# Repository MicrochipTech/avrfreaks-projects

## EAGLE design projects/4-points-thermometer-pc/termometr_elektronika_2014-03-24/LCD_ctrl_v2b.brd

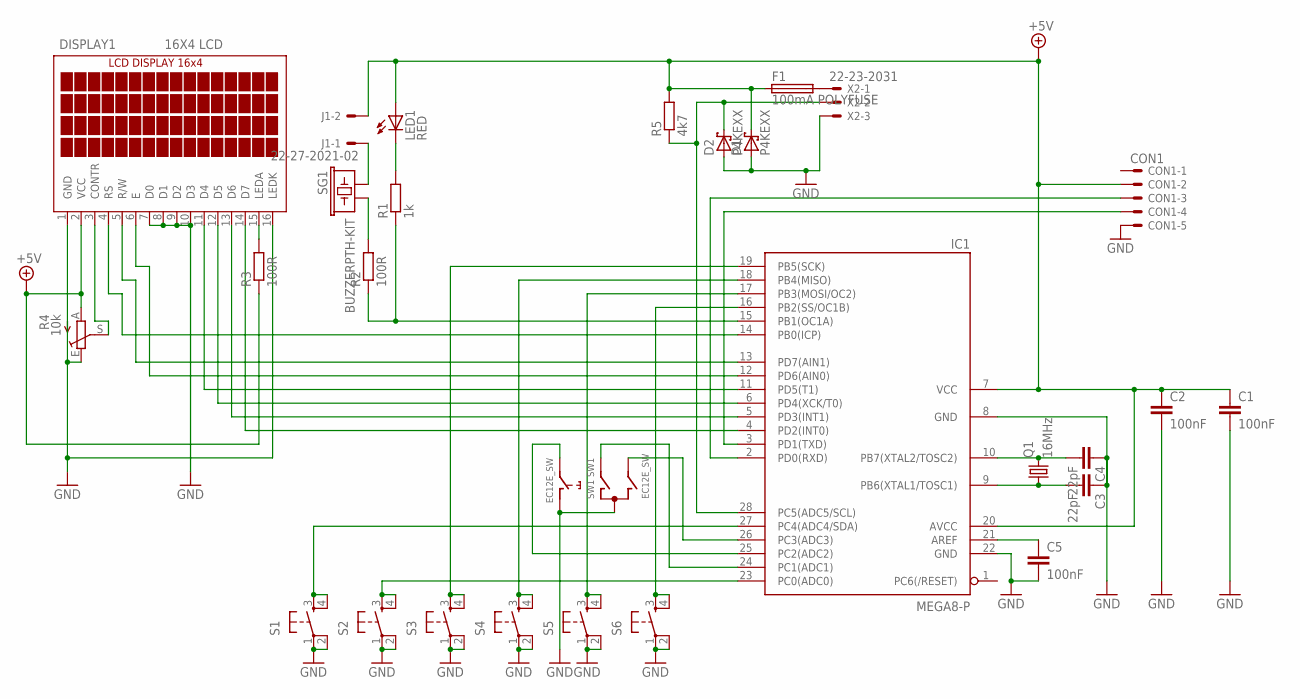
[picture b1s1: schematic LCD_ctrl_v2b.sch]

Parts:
C1, C2, C5: 100nF; C050-025X075
C3, C4: 22pF; C050-025X075
CON1: CON1; 22-23-2051
D1, D2: P4KEXX; DO41-10
DISPLAY1: 16X4 LCD; LCD-AC-1604A-BIG_PADS
F1: 100mA POLYFUSE; TE5
IC1: MEGA8-P; DIL28-3
J1: 22-27-2021-02; 6410-02
LED1: RED; LED3MM
Q1: 16MHz; HC49/S
R1: 1k; 0204/7
R2, R3: 100R; 0204/7
R4: 10k; CA6H
R5: 4k7; 0204/7
S1, S2, S3, S4, S5, S6: TAC_SWITCHPTH; TACTILE-PTHX
SG1: BUZZERPTH-KIT; BUZZER-12MM-KIT
SW1: EC12E_SW; ALPS_EC12E_SW
X2: 22-23-2031

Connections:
+5V: C1.1, C2.1, CON1.2, D1.C, DISPLAY1.2 (VCC), F1.1, IC1.7 (VCC), IC1.20 (AVCC), J1.2, LED1.A, R3.1, R4.A, R5.2
GND: C1.2, C2.2, C3.1, C4.1, C5.2, CON1.5, D1.A, D2.A, DISPLAY1.1 (GND), DISPLAY1.7 (D0), DISPLAY1.8 (D1), DISPLAY1.9 (D2), DISPLAY1.10 (D3), DISPLAY1.16 (LEDK), IC1.8 (GND), IC1.22 (GND), R4.E, S1.1, S1.2, S2.1, S2.2, S3.1, S3.2, S4.1, S4.2, S5.1, S5.2, S6.1, S6.2, SW1.C, SW1.D (1), X2.3
unnamed: C5.1, IC1.21 (AREF)
unnamed: F1.2, X2.1
unnamed: C4.2, IC1.10 (PB7(XTAL2/TOSC2)), Q1.2
unnamed: C3.2, IC1.9 (PB6(XTAL1/TOSC1)), Q1.1
unnamed: CON1.4, IC1.3 (PD1(TXD))
unnamed: CON1.3, IC1.2 (PD0(RXD))
unnamed: DISPLAY1.14 (D7), IC1.4 (PD2(INT0))
unnamed: DISPLAY1.13 (D6), IC1.5 (PD3(INT1))
unnamed: DISPLAY1.12 (D5), IC1.6 (PD4(XCK/T0))
unnamed: DISPLAY1.11 (D4), IC1.11 (PD5(T1))
unnamed: IC1.23 (PC0(ADC0)), S2.3, S2.4
unnamed: DISPLAY1.3 (CONTR), R4.S
unnamed: R2.2, SG1.- (2)
unnamed: DISPLAY1.6 (E), IC1.12 (PD6(AIN0))
unnamed: DISPLAY1.5 (R/W), IC1.13 (PD7(AIN1))
unnamed: LED1.K (C), R1.2
unnamed: DISPLAY1.4 (RS), IC1.14 (PB0(ICP))
unnamed: IC1.19 (PB5(SCK)), S3.3, S3.4
unnamed: IC1.18 (PB4(MISO)), S4.3, S4.4
unnamed: IC1.17 (PB3(MOSI/OC2)), S5.3, S5.4
unnamed: IC1.16 (PB2(SS/OC1B)), S6.3, S6.4
unnamed: IC1.24 (PC1(ADC1)), SW1.A
unnamed: J1.1, SG1.+ (1)
unnamed: DISPLAY1.15 (LEDA), R3.2
unnamed: IC1.25 (PC2(ADC2)), SW1.E (2)
unnamed: IC1.26 (PC3(ADC3)), SW1.B
unnamed: IC1.27 (PC4(ADC4/SDA)), S1.3, S1.4
unnamed: D2.C, IC1.28 (PC5(ADC5/SCL)), R5.1, X2.2
unnamed: IC1.15 (PB1(OC1A)), R1.1, R2.1

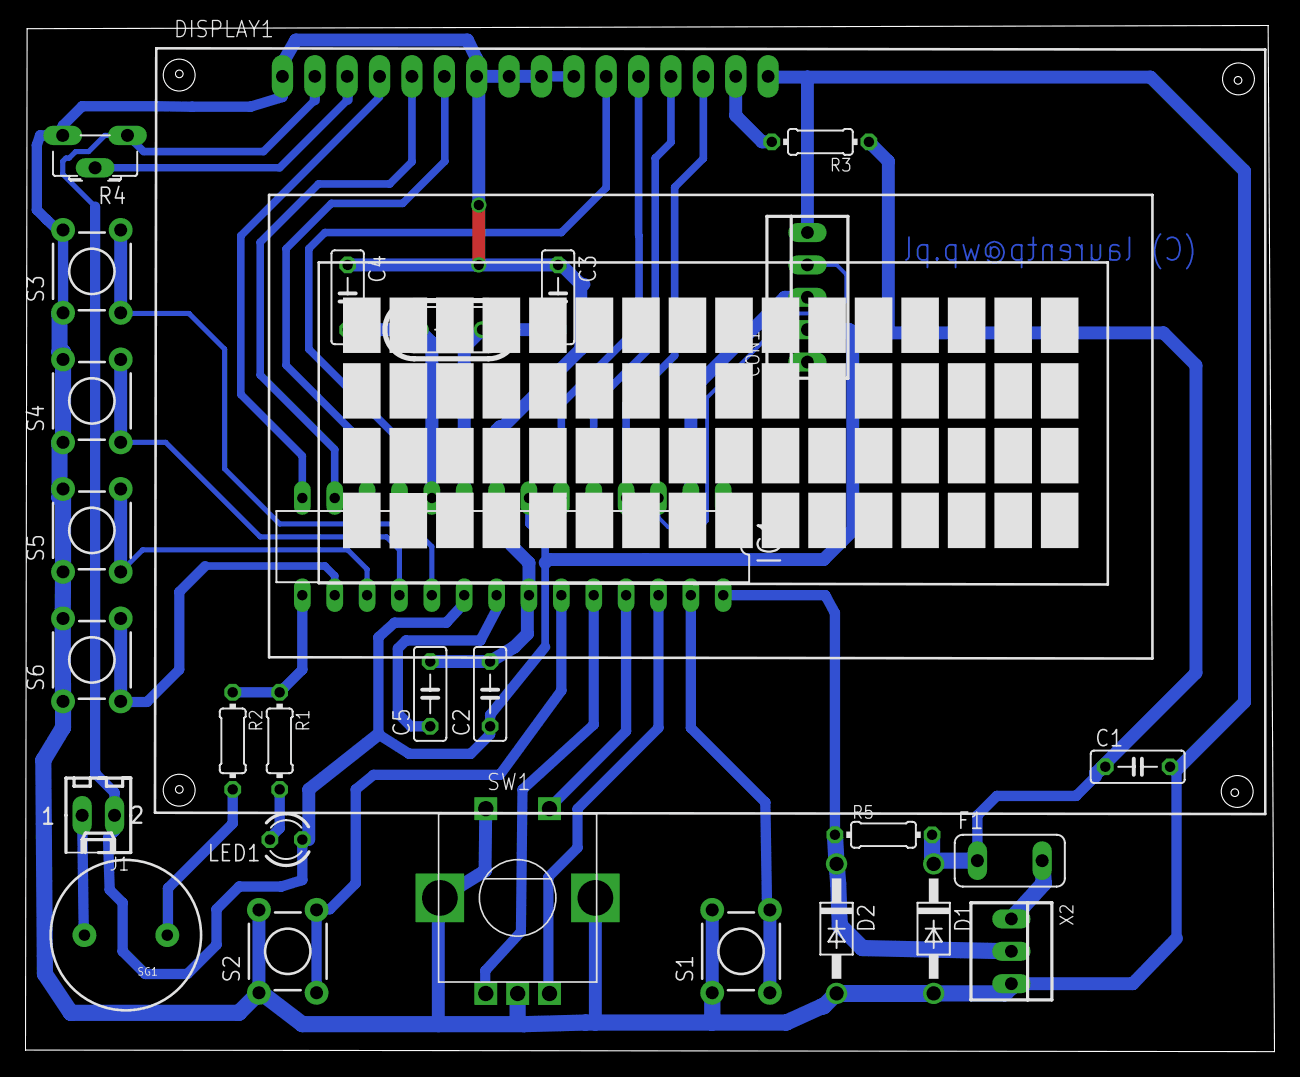
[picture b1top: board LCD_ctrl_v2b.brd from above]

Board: 2 copper layers, 98.0 x 80.5 mm, 28 parts (0 on the bottom side), 31 nets.

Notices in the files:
parts and their libraries:
SparkFun-Electromechanical: Licensing: CC v3.0 Share-Alike You are welcome to use this library for commercial purposes.
